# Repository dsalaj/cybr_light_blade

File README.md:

<div align="center">

```
 ██╗     ██╗ ██████╗ ██╗  ██╗████████╗    ██████╗ ██╗      █████╗ ██████╗ ███████╗
 ██║     ██║██╔════╝ ██║  ██║╚══██╔══╝    ██╔══██╗██║     ██╔══██╗██╔══██╗██╔════╝
 ██║     ██║██║  ███╗███████║   ██║       ██████╔╝██║     ███████║██║  ██║█████╗
 ██║     ██║██║   ██║██╔══██║   ██║       ██╔══██╗██║     ██╔══██║██║  ██║██╔══╝
 ███████╗██║╚██████╔╝██║  ██║   ██║       ██████╔╝███████╗██║  ██║██████╔╝███████╗
 ╚══════╝╚═╝ ╚═════╝ ╚═╝  ╚═╝   ╚═╝       ╚═════╝ ╚══════╝╚═╝  ╚═╝╚═════╝ ╚══════╝
          >>  DIY_CYBERPUNK  //  LGHT_BLD  //  WS2811 PIXEL SWORD  <<
```

*A 356 mm, sword-shaped, daisy-chainable LED board. It plugs into a WLED / Elite 4D-EXMU controller like an ordinary pixel strip.*

</div>

---

## `> SYS.INFO`

Each blade carries **12 small 0805 LEDs** and **6 glowing 38 mm LED filaments**. Ten **WS2811** driver chips control them, so the controller sees each blade as **10 standard RGB pixels**. Chain as many blades as your power supply can feed: data comes in on `IN` and goes out on `OUT`, one blade after another.

| `PARAM`        | `VALUE`                                                     |
|----------------|-------------------------------------------------------------|
| Outline        | 356 × 65 mm sword: hilt, 45° guard, slotted blade, bevelled tip |
| Stackup        | 2 layers, 1.6 mm, black soldermask, white silkscreen        |
| Drivers        | 10 × Worldsemi WS2811 (SOP-8), constant-current 18.5 mA outputs |
| Light          | 12 × 0805 white LEDs + 6 × 3 V / 38 mm filaments            |
| Protocol       | WS281x single wire, 800 kHz (SET pin left floating)         |
| Supply         | 5 V, ≈ 0.58 A per blade at full white                       |
| I/O            | 2 × JST XH 3-pin, right-angle (`IN` / `OUT`)                |
| Mounting       | 2 × M5 (2020 extrusion) + 4 × M3 (diffuser), copper-free keepouts |

---

## `> VISUAL.FEED`

<div align="center">

**`[ TOP ]`**

**`[ BOTTOM ]`**: solid GND plane, with the data chain hopping along it

</div>

---

## `> PIXEL.MAP`

Data flows chip to chip in this order. Each WS2811 is one pixel in WLED.

```mermaid
flowchart LR
    IN([J1 IN]) --> U1 --> U2 --> U3 --> U4 --> U5 --> U6 --> U7 --> U8 --> U9 --> U10 --> OUT([J2 OUT])
    classDef chip fill:#0d0221,stroke:#ff00ff,color:#00f0ff
    classDef io fill:#ff00ff,stroke:#00f0ff,color:#0d0221
    class U1,U2,U3,U4,U5,U6,U7,U8,U9,U10 chip
    class IN,OUT io
```

| Pixel | Chip | Drives | How to light it |
|:-----:|:----:|--------|-----------------|
| 1 | U1 | D1 · D2 · D3 on R · G · B | each channel is one LED |
| 2 | U2 | D4 · D5 · D6 | ″ |
| 3 | U3 | D7 · D8 · D9 | ″ |
| 4 | U4 | D10 · D17 · D18 | ″ |
| 5–10 | U5–U10 | filaments D11–D16, one per chip | **use white / grey (R = G = B)** |

> [!TIP]
> On the filament pixels all three outputs are tied together, giving about 55 mA per filament. The channels add up, so the brightness follows R + G + B. Colour values do nothing there; only the total level matters.

---

## `> JACK.IN`

```
        ┌──────────────┐
  pin 1 │  ■  +5V      │   silkscreen: 5V
  pin 2 │  ●  DATA     │   silkscreen: D
  pin 3 │  ●  GND      │   silkscreen: G
        └──────────────┘   same pinout on IN and OUT
```

- **Blade to blade:** JST XH 3-pin cable, female–female, straight through (pin 1 to pin 1).
- **Controller to first blade:** JST XH 3-pin pigtail. The bare wires go into the controller's screw terminals.

> [!WARNING]
> **There is no reverse-polarity protection.** A "reversed" XH cable swaps +5V and GND and kills the WS2811s and the bulk cap. Check every cable pin 1 to pin 1 with a multimeter before first power-up.

---

## `> POWER.GRID`

| Load | Current |
|------|--------:|
| 12 × 0805 LED × 18.5 mA | ≈ 222 mA |
| 6 × filament × ~55 mA | ≈ 330 mA |
| 10 × WS2811 quiescent | ≈ 30 mA |
| **Per blade, full white** | **≈ 0.58 A** |

The XH contacts are rated 3 A, so one feed powers about **5 blades**. For longer chains, inject 5 V partway along. Every chip gets its own 100 Ω + 100 nF filter on VDD, and each DIN has a 33 Ω series resistor against reflections and hot-plug spikes.

> [!NOTE]
> The WS2811 data input needs about 3.5 V (0.7 × VDD). If your controller outputs 3.3 V logic without a level shifter, the first blade may flicker.

---

## `> FAB.PIPELINE`

Assembly is done by **PCBWay**. You hand-solder the filaments yourself.

1. **Latest production set:** [`light_blade/pcbway_production/2026-10-18-12-11-58/`](light_blade/pcbway_production/2026-10-18-12-11-58/)

   | File | What it is |
   |------|------------|
   | `light_blade.kicad_pcb_gerber.zip` | Gerbers + drill files |
   | `light_blade_BOM_PCBWay.xlsx` | BOM rev 3 in PCBWay's template, with full manufacturer part numbers |
   | `light_blade_positions.csv` | Pick-and-place file, unique designators |
   | `light_blade.kicad_pcb_netlist.ipc` | IPC-356 netlist for electrical test |

2. **The filaments are not assembled by PCBWay.** D11–D16 are left out of the BOM and the positions file, and their pads stay empty. Solder them after delivery. Pad 1 is − (cathode) and pad 2 is + (anode), as marked on the silkscreen.

3. **To regenerate the outputs,** open `light_blade.kicad_pcb` in KiCad and run **PCBWay Fabrication Toolkit** from the plugin toolbar.

### Bill of materials

| Ref | Qty | Part | Mfr · MPN |
|-----|:---:|------|-----------|
| U1–U10 | 10 | LED driver, SOP-8 | Worldsemi · `WS2811` |
| D1–D10, D17, D18 | 12 | LED white 0805 | KENTO · `KT-0805W` |
| C1–C10 | 10 | 100 nF X7R 50 V 0805 | Samsung · `CL21B104KBCNNNC` |
| C11 | 1 | 470 µF 10 V electrolytic, 8 × 10.2 mm | Panasonic · `EEE-FK1A471P` |
| R1–R10, R21 | 11 | 33 Ω 1 % 0805 | YAGEO · `RC0805FR-0733RL` |
| R11–R20 | 10 | 100 Ω 1 % 0805 | YAGEO · `RC0805FR-07100RL` |
| J1, J2 | 2 | JST XH 3P right-angle | JST · `S3B-XH-A(LF)(SN)` |
| D11–D16 | 6 | LED filament 3 V 38 mm | *hand-soldered, not in the BOM* |

---

## `> FILE.TREE`

```
.
├── light_blade/
│   ├── light_blade.kicad_pro         ← open this in KiCad 10
│   ├── light_blade.kicad_sch         ← schematic
│   ├── light_blade.kicad_pcb         ← layout
│   ├── light_blade.pretty/           ← custom LED_Filament_38mm footprint
│   ├── fab_gerber/                   ← plain KiCad gerber export
│   └── pcbway_production/            ← timestamped PCBWay order packages
├── docs/                             ← renders used in this README
├── light_blade_plan_v1.md            ← design notes & decisions
└── Sample_BOM_PCBWay.xlsx            ← PCBWay's BOM template
```

---

## `> STATUS`

- [x] Schematic + layout, DRC clean
- [x] BOM with full MPNs, unique designators
- [x] Copper keepouts at mounting holes, tight decoupling on every chip
- [ ] PCBWay order: rev 3 files ready to send
- [ ] Measure the real filaments: tab spacing (footprint pitch is 36 mm), polarity and current
- [ ] Confirm the controller's data voltage on the chosen port
- [ ] First light 🔥

---

<div align="center">

```
 ░▒▓█  WAKE UP. THE CITY NEEDS MORE LIGHT.  █▓▒░
```

<sub>Designed in KiCad · assembled by PCBWay · lit by WS2811</sub>

</div>

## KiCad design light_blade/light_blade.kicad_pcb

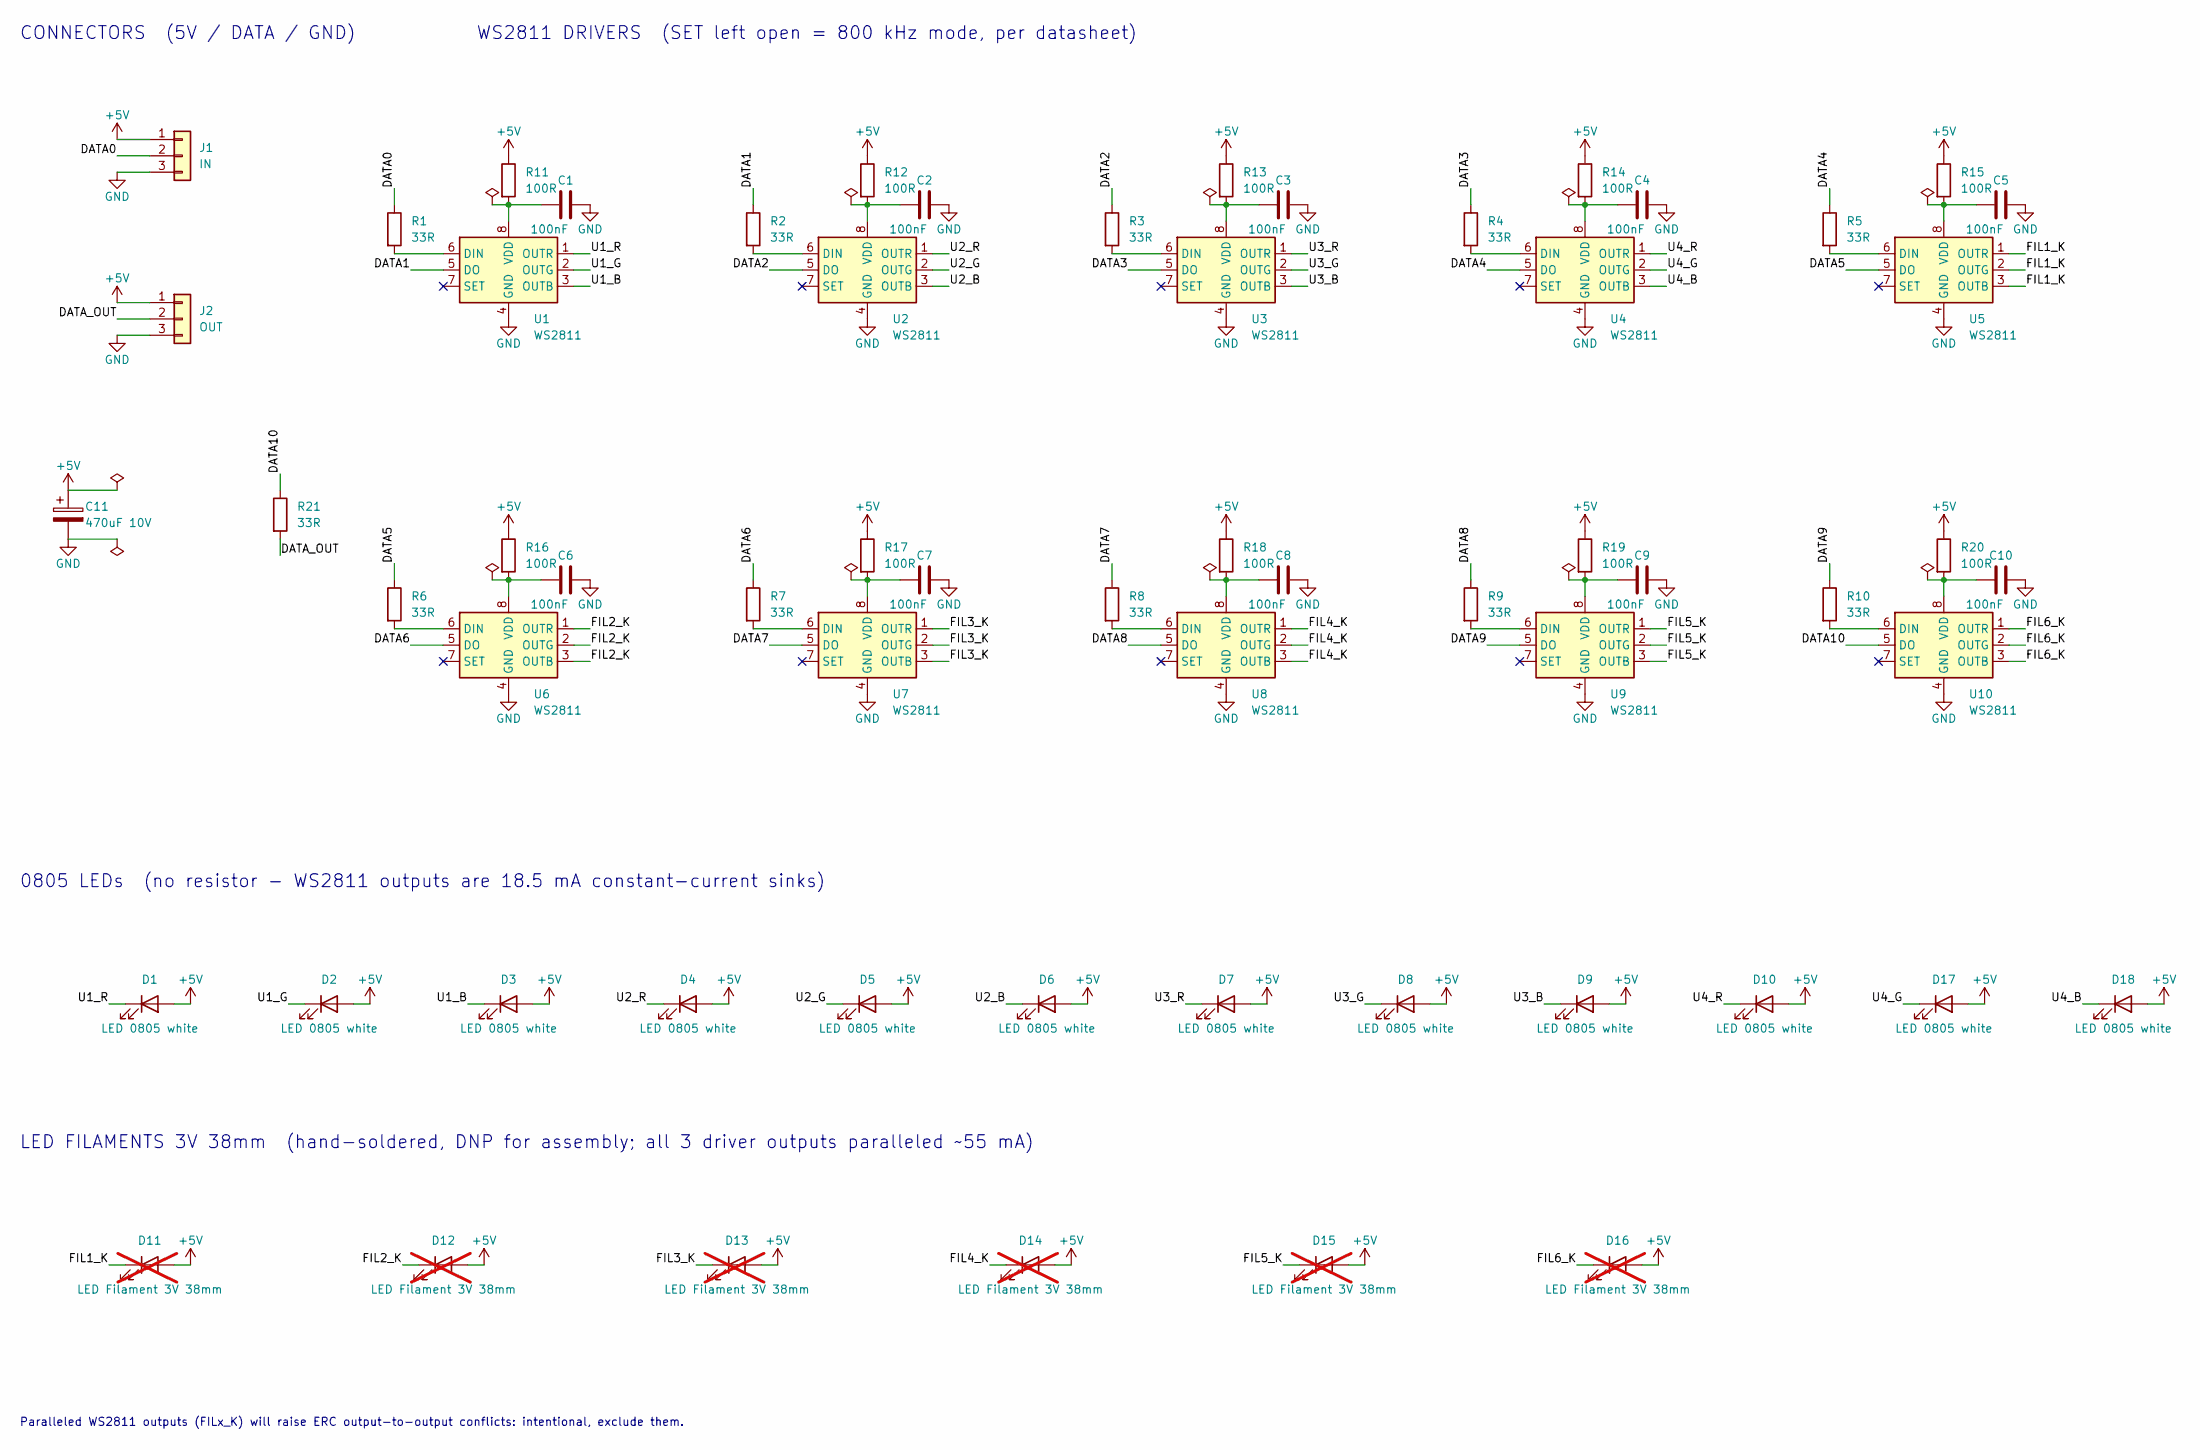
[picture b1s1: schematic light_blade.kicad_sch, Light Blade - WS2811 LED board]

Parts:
C1, C2, C3, C4, C5, C6, C7, C8, C9, C10: 100nF; C_0805_2012Metric
C11: 470uF 10V; CP_Elec_8x10
D1, D2, D3, D4, D5, D6, D7, D8, D9, D10, D17, D18: LED 0805 white; LED_0805_2012Metric
D11, D12, D13, D14, D15, D16: LED Filament 3V 38mm; LED_Filament_38mm; not fitted
J1: IN; JST_XH_S3B-XH-A_1x03_P2.50mm_Horizontal; MPN S3B-XH-A (or XH-3AW clone)
J2: OUT; JST_XH_S3B-XH-A_1x03_P2.50mm_Horizontal; MPN S3B-XH-A (or XH-3AW clone)
R1, R2, R3, R4, R5, R6, R7, R8, R9, R10, R21: 33R; R_0805_2012Metric
R11, R12, R13, R14, R15, R16, R17, R18, R19, R20: 100R; R_0805_2012Metric
U1, U2, U3, U4, U5, U6, U7, U8, U9, U10: WS2811; SOIC-8_3.9x4.9mm_P1.27mm

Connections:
+5V: C11.1, D1.2 (A), D2.2 (A), D3.2 (A), D4.2 (A), D5.2 (A), D6.2 (A), D7.2 (A), D8.2 (A), D9.2 (A), D10.2 (A), D11.2 (A), D12.2 (A), D13.2 (A), D14.2 (A), D15.2 (A), D16.2 (A), D17.2 (A), D18.2 (A), J1.1, J2.1, R11.1, R12.1, R13.1, R14.1, R15.1, R16.1, R17.1, R18.1, R19.1, R20.1
/DATA0: J1.2, R1.1
/DATA1: R2.1, U1.5 (DO)
/DATA2: R3.1, U2.5 (DO)
/DATA3: R4.1, U3.5 (DO)
/DATA4: R5.1, U4.5 (DO)
/DATA5: R6.1, U5.5 (DO)
/DATA6: R7.1, U6.5 (DO)
/DATA7: R8.1, U7.5 (DO)
/DATA8: R9.1, U8.5 (DO)
/DATA9: R10.1, U9.5 (DO)
/DATA10: R21.1, U10.5 (DO)
/DATA_OUT: J2.2, R21.2
/FIL1_K: D11.1 (K), U5.1 (OUTR), U5.2 (OUTG), U5.3 (OUTB)
/FIL2_K: D12.1 (K), U6.1 (OUTR), U6.2 (OUTG), U6.3 (OUTB)
/FIL3_K: D13.1 (K), U7.1 (OUTR), U7.2 (OUTG), U7.3 (OUTB)
/FIL4_K: D14.1 (K), U8.1 (OUTR), U8.2 (OUTG), U8.3 (OUTB)
/FIL5_K: D15.1 (K), U9.1 (OUTR), U9.2 (OUTG), U9.3 (OUTB)
/FIL6_K: D16.1 (K), U10.1 (OUTR), U10.2 (OUTG), U10.3 (OUTB)
/U1_B: D3.1 (K), U1.3 (OUTB)
/U1_G: D2.1 (K), U1.2 (OUTG)
/U1_R: D1.1 (K), U1.1 (OUTR)
/U2_B: D6.1 (K), U2.3 (OUTB)
/U2_G: D5.1 (K), U2.2 (OUTG)
/U2_R: D4.1 (K), U2.1 (OUTR)
/U3_B: D9.1 (K), U3.3 (OUTB)
/U3_G: D8.1 (K), U3.2 (OUTG)
/U3_R: D7.1 (K), U3.1 (OUTR)
/U4_B: D18.1 (K), U4.3 (OUTB)
/U4_G: D17.1 (K), U4.2 (OUTG)
/U4_R: D10.1 (K), U4.1 (OUTR)
GND: C1.2, C2.2, C3.2, C4.2, C5.2, C6.2, C7.2, C8.2, C9.2, C10.2, C11.2, J1.3, J2.3, U1.4 (GND), U2.4 (GND), U3.4 (GND), U4.4 (GND), U5.4 (GND), U6.4 (GND), U7.4 (GND), U8.4 (GND), U9.4 (GND), U10.4 (GND)
unnamed: R1.2, U1.6 (DIN)
unnamed: C1.1, R11.2, U1.8 (VDD)
unnamed: R2.2, U2.6 (DIN)
unnamed: C2.1, R12.2, U2.8 (VDD)
unnamed: R3.2, U3.6 (DIN)
unnamed: C3.1, R13.2, U3.8 (VDD)
unnamed: R4.2, U4.6 (DIN)
unnamed: C4.1, R14.2, U4.8 (VDD)
unnamed: R5.2, U5.6 (DIN)
unnamed: C5.1, R15.2, U5.8 (VDD)
unnamed: R6.2, U6.6 (DIN)
unnamed: C6.1, R16.2, U6.8 (VDD)
unnamed: R7.2, U7.6 (DIN)
unnamed: C7.1, R17.2, U7.8 (VDD)
unnamed: R8.2, U8.6 (DIN)
unnamed: C8.1, R18.2, U8.8 (VDD)
unnamed: R9.2, U9.6 (DIN)
unnamed: C9.1, R19.2, U9.8 (VDD)
unnamed: R10.2, U10.6 (DIN)
unnamed: C10.1, R20.2, U10.8 (VDD)

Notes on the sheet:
CONNECTORS (5V / DATA / GND)
WS2811 DRIVERS (SET left open = 800 kHz mode, per datasheet)
0805 LEDs (no resistor - WS2811 outputs are 18.5 mA constant-current sinks)
LED FILAMENTS 3V 38mm (hand-soldered, DNP for assembly; all 3 driver outputs paralleled ~55 mA)
Paralleled WS2811 outputs (FILx_K) will raise ERC output-to-output conflicts: intentional, exclude them.

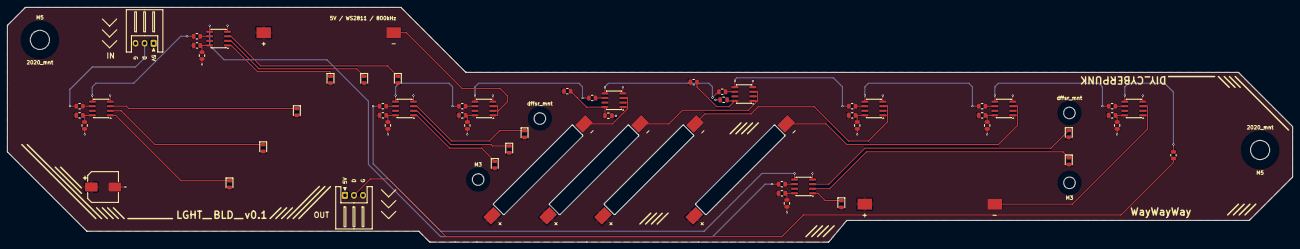
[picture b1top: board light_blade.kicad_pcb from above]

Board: 2 copper layers, 356.0 x 65.0 mm, 68 parts (0 on the bottom side), 52 nets.

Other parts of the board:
2020_mnt, 2020_mnt#2: MountingHole_5.3mm_M5
M3, M3#2: MountingHole_3.2mm_M3
dffsr_mnt: MountingHole_3.2mm_M3
dffsr_mnt#2: MountingHole_3.2mm_M3

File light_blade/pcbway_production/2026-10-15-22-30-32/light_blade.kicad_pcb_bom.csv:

Designator,Quantity,Value,Footprint,Package,MPN,DNP,Mount_Type,KiLib_Generator
"C1, C10, C2, C3, C4, C5, C6, C7, C8, C9",10,100nF,C_0805_2012Metric,,,,smt,SMD_2terminal_chip_molded
C11,1,470uF 10V,CP_Elec_8x10,,,,smt,capacitor/SMD/elec_round_polarized
"D1, D10, D10, D10, D2, D3, D4, D5, D6, D7, D8, D9",12,LED 0805 white,LED_0805_2012Metric,,,,smt,SMD_2terminal_chip_molded
D11,1,LED Filament 3V 38mm,LED_Filament_38mm,,,Yes,smt,
D12,1,LED Filament 3V 38mm,LED_Filament_38mm,,,Yes,smt,
D13,1,LED Filament 3V 38mm,LED_Filament_38mm,,,Yes,smt,
D14,1,LED Filament 3V 38mm,LED_Filament_38mm,,,Yes,smt,
D15,1,LED Filament 3V 38mm,LED_Filament_38mm,,,Yes,smt,
D16,1,LED Filament 3V 38mm,LED_Filament_38mm,,,Yes,smt,
J1,1,IN,JST_XH_S3B-XH-A_1x03_P2.50mm_Horizontal,,S3B-XH-A (or XH-3AW clone),,tht,connector/JST
J2,1,OUT,JST_XH_S3B-XH-A_1x03_P2.50mm_Horizontal,,S3B-XH-A (or XH-3AW clone),,tht,connector/JST
"R1, R10, R2, R21, R3, R4, R5, R6, R7, R8, R9",11,33R,R_0805_2012Metric,,,,smt,SMD_2terminal_chip_molded
"R11, R12, R13, R14, R15, R16, R17, R18, R19, R20",10,100R,R_0805_2012Metric,,,,smt,SMD_2terminal_chip_molded
"U1, U10, U2, U3, U4, U5, U6, U7, U8, U9",10,WS2811,SOIC-8_3.9x4.9mm_P1.27mm,,,,smt,package/gullwing
